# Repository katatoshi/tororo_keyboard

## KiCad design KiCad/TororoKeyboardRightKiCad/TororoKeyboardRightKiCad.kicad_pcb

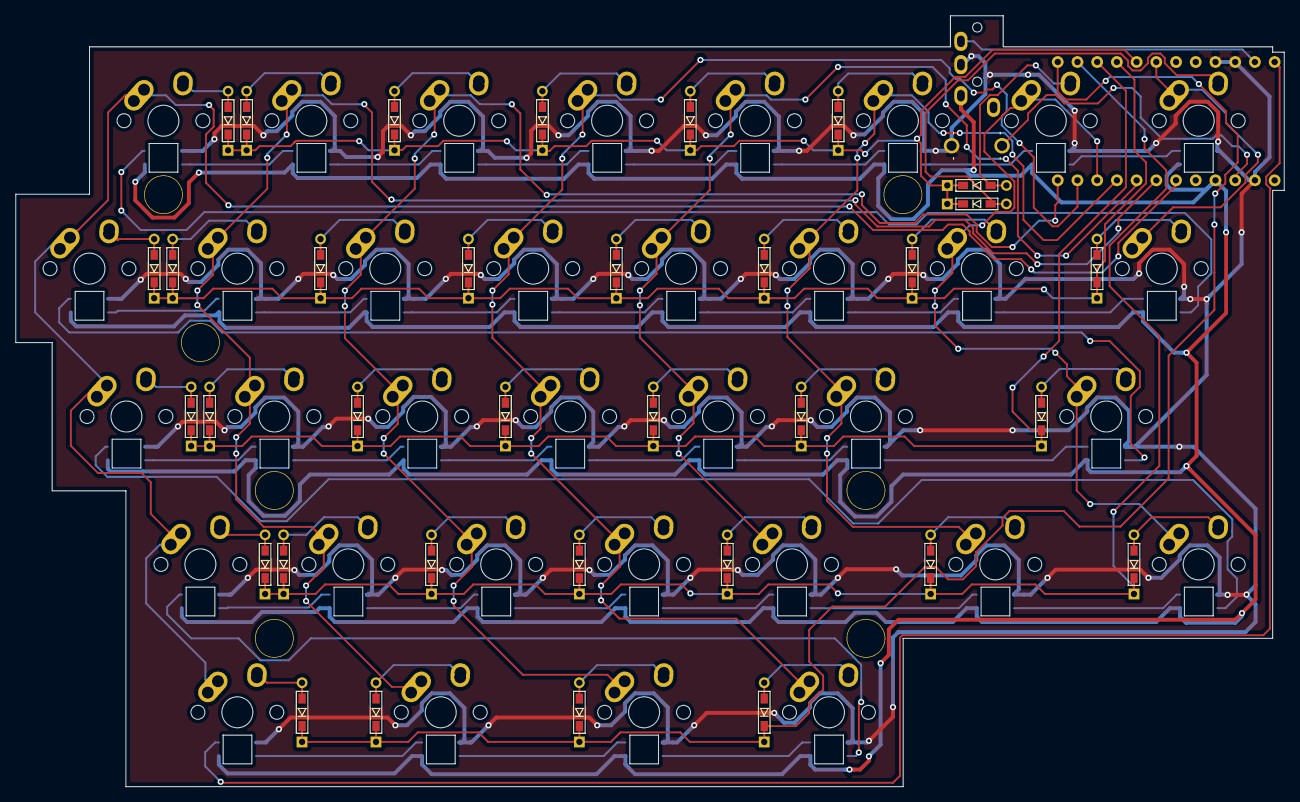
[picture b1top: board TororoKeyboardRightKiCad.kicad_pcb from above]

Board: 2 copper layers, 163.4 x 99.3 mm, 112 parts (0 on the bottom side), 85 nets.

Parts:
D1, D2, D3, D4, D5, D6, D7, D8, D9, D10, D11, D12, D13, D14, D15, D16, D17, D18, D19, D20, D21, D22, D23, D24, D25, D26, D27, D28, D29, D30, D31, D32, D33, D34: D; D3_TH_SMD_top
J1: MJ-4PP-9; MJ-4PP-9_back
L1, L2, L3, L4, L5, L6, L7, L8, L9, L10, L11, L12, L13, L14, L15, L16, L17, L18, L19, L20, L21, L22, L23, L24, L25, L26, L27, L28, L29, L30, L31, L32, L33, L34: SK6812MINI; SK6812MINI_back
RSW1: SW_Push; ResetSW_back
Ref**: Val**; HOLE
Ref**#2, Ref**#3, Ref**#4, Ref**#5, Ref**#6, Ref**#7: Val**; HOLE
SW1, SW2, SW3, SW4, SW5, SW6, SW7, SW8, SW9, SW10, SW11, SW12, SW13, SW14, SW15, SW16, SW17, SW18, SW19, SW20, SW21, SW22, SW23, SW24, SW25, SW26, SW27, SW28, SW29, SW30, SW31, SW32, SW33, SW34: SW_PUSH; Hybrid_PCB_100H_no-silk_no_ref
U1: ProMicro; ProMicro_v2_back_right

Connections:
GND: J1.C, L1.2, L2.2, L3.2, L4.2, L5.2, L6.2, L7.2, L8.2, L9.2, L10.2, L11.2, L12.2, L13.2, L14.2, L15.2, L16.2, L17.2, L18.2, L19.2, L20.2, L21.2, L22.2, L23.2, L24.2, L25.2, L26.2, L27.2, L28.2, L29.2, L30.2, L31.2, L32.2, L33.2, L34.2, RSW1.2, U1.3, U1.4, U1.23
unnamed: D1.2, SW1.2
unnamed: D2.2, SW2.2
unnamed: D3.2, SW3.2
unnamed: D4.2, SW4.2
unnamed: D5.2, SW5.2
unnamed: D6.2, SW6.2
unnamed: D7.2, SW7.2
unnamed: D8.2, SW8.2
unnamed: D9.2, SW9.2
unnamed: D10.2, SW10.2
unnamed: D11.2, SW11.2
unnamed: D12.2, SW12.2
unnamed: D13.2, SW13.2
unnamed: D14.2, SW14.2
unnamed: D15.2, SW15.2
unnamed: D16.2, SW16.2
unnamed: D17.2, SW17.2
unnamed: D18.2, SW18.2
unnamed: D19.2, SW19.2
unnamed: D20.2, SW20.2
unnamed: D21.2, SW21.2
unnamed: D22.2, SW22.2
unnamed: D23.2, SW23.2
unnamed: D24.2, SW24.2
unnamed: D25.2, SW25.2
unnamed: D26.2, SW26.2
unnamed: D27.2, SW27.2
unnamed: D28.2, SW28.2
unnamed: D29.2, SW29.2
unnamed: D30.2, SW30.2
unnamed: D31.2, SW31.2
unnamed: D32.2, SW32.2
unnamed: D33.2, SW33.2
unnamed: D34.2, SW34.2
unnamed: L1.1, L6.3
unnamed: L1.3, L34.1
unnamed: L2.1, L7.3
unnamed: L2.3, L31.1
unnamed: L3.1, L8.3
unnamed: L3.3, L32.1
unnamed: L4.1, L9.3
unnamed: L10.1, L15.3
unnamed: L5.1, L10.3
unnamed: L11.1, L16.3
unnamed: L6.1, L11.3
unnamed: L12.1, L17.3
unnamed: L7.1, L12.3
unnamed: L13.1, L18.3
unnamed: L8.1, L13.3
unnamed: L14.1, L19.3
unnamed: L9.1, L14.3
unnamed: L15.1, L20.3
unnamed: L16.1, L21.3
unnamed: L17.1, L22.3
unnamed: L18.1, L23.3
unnamed: L19.1, L24.3
unnamed: L4.3, L20.1
unnamed: L21.1, L25.3
unnamed: L22.1, L26.3
unnamed: L23.1, L27.3
unnamed: L24.1, L28.3
unnamed: L25.1, L29.3
unnamed: L26.1, L30.3
unnamed: L27.1, L31.3
unnamed: L28.1, L32.3
unnamed: L29.1, L33.3
unnamed: L30.1, L34.3
VCC: J1.D, L1.4, L2.4, L3.4, L4.4, L5.4, L6.4, L7.4, L8.4, L9.4, L10.4, L11.4, L12.4, L13.4, L14.4, L15.4, L16.4, L17.4, L18.4, L19.4, L20.4, L21.4, L22.4, L23.4, L24.4, L25.4, L26.4, L27.4, L28.4, L29.4, L30.4, L31.4, L32.4, L33.4, L34.4, U1.21
col1: SW33.1, SW34.1, U1.7
col2: SW29.1, SW30.1, SW31.1, SW32.1, U1.15
col3: SW25.1, SW26.1, SW27.1, SW28.1, U1.16
col4: SW21.1, SW22.1, SW23.1, SW24.1, U1.17
col5: SW16.1, SW17.1, SW18.1, SW19.1, SW20.1, U1.14
col6: SW11.1, SW12.1, SW13.1, SW14.1, SW15.1, U1.13
col7: SW6.1, SW7.1, SW8.1, SW9.1, SW10.1, U1.18
col8: SW1.1, SW2.1, SW3.1, SW4.1, SW5.1, U1.19
data: J1.B, U1.2
led: L5.3, U1.1
reset: RSW1.1, U1.22
row1: D1.1, D6.1, D11.1, D16.1, D21.1, D25.1, D29.1, D33.1, U1.8
row2: D2.1, D7.1, D12.1, D17.1, D22.1, D26.1, D30.1, D34.1, U1.9
row3: D3.1, D8.1, D13.1, D18.1, D23.1, D27.1, D31.1, U1.10
row4: D4.1, D9.1, D14.1, D19.1, D24.1, D28.1, D32.1, U1.11
row5: D5.1, D10.1, D15.1, D20.1, U1.12

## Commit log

2019-10-22 レイアウト json ファイルを追加
2019-10-22 キースイッチの scad ファイルを追加
2019-10-22 左手側の scad データを追加
2019-10-22 右側の scad データを追加
2019-10-23 左手側の Pro Micro スペース、trrs ジャックスペース、リセットスイッチホールを追加
    位置の確認用に Pro Micro, trrs ジャックの大きさの cube も表示。
2019-10-23 右手側の Pro Micro スペース、trrs ジャックスペース、リセットスイッチホールを追加
    位置の確認用に Pro Micro, trrs ジャックの大きさの cube も表示。
2019-10-23 左手側のネジ穴を追加
    位置の確認用にスペーサー等も追加。
2019-10-23 右手側のネジ穴を追加
    位置の確認用にスペーサー等も追加。
2019-10-23 左右を同時に表示したイメージを作成
2019-10-29 プレートをA5, A3のアクリルプレートに射影するmoduleを作成
2019-10-29 各プレートのdxfファイルを追加
2019-10-29 左手側のKiCadプロジェクトを追加
    回路図まで作成。
2019-10-30 フットプリントライブラリを追加
    kdb.pretty, Keebio-Parts.pretty のカスタム。
2019-10-30 左手側の回路図を整理しネットリストを追加
2019-10-30 右手側基板の KiCad プロジェクトを追加し、回路図とネットリストを作成
2019-10-30 KiCad プロジェクトを KiCad ディレクトリに移動
2019-10-30 .gitignore 追加
    KiCad の .bak ファイルと fp-info-cache ファイルは管理しない。
2019-10-30 キースイッチのフットプリントを微修正
    kbd を参考に 3D 表示したときに穴があいて見えるようにした。
2019-10-30 左手側pcbのモデルを完成させた
2019-10-30 右手側pcbのモデルを完成させた
2019-10-30 左手基板のdxfファイルを出力
2019-10-30 右手基板のdxfファイルを出力
2019-10-30 左手側のレイアウト作成
    TODO: 配線
2019-10-30 SK6812MINIの穴の高さを小さくした
    全体的にきつきつだったので余裕があるこの穴の高さを小さくした。
2019-10-30 レイアウトを微調整
2019-11-02 左手側の配線を整理
2019-11-02 表の塗りつぶしがうまく回るように配線を修正
2019-11-02 裏の塗りつぶしがうまく回るように配線を修正
2019-11-02 DRCに指摘されたのでパッドとの距離を調整
2019-11-02 GNDを塗りつぶし
2019-11-02 キーボード名とクレジットを配置
2019-11-02 gerberファイル出力ディレクトリはバージョン管理外とする
2019-11-02 不要なテキストを除去
2019-11-03 .kicad_pcb-bak ファイルを管理対象外にした
2019-11-03 右手側のレイアウト作成
    TODO: 配線
2019-11-03 pro micro のフットプリントを右手用に修正してレイアウトを更新
    文字の位置を変更した。
2019-11-06 右手側の配線を整理
2019-11-06 左手のキーボード名とクレジットのサイズと位置を調整
2019-11-06 左手側の配線を修正
2019-11-06 寸法線を追加
2019-11-07 左手側の配線を再度修正
